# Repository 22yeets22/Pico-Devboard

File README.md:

<h1 align="center">
  Pico+ Devboard
  <br>
</h1>

<h4 align="center">
A pico sized custom rp2040 devboard, but with 16MB flash and a lot of extra features!
</h4>
<br>

<div align="center">

| Front Render                            | PCB                    |
| --------------------------------------- | ---------------------- |
|  |  |

</div>

## Motivation

I wanted a more capable RP2040 board with significantly more flash memory and USB-C. Most dev boards limit storage and input options, so I designed one that supports USB-C, battery input, higher current capability, and voltage monitoring while staying in the same form factor.

## Features

- RP2040 microcontroller
- 16MB QSPI Flash
- USB-C
- Battery input (Schottky diode OR-ing with USB)
- 500mA LDO (10V max input)
- VSYS voltage monitoring via resistor divider on ADC3
- Onboard power LED
- Onboard GPIO25 LED
- Bootsel + Reset button
- Fully labeled GPIO pins

## Future Improvements

- Buck-boost regulator for better efficiency + larger voltage range
- Exposed VSYS pin
- 3V3_EN pin breakout

## How to Use

Like a normal Pico:

1. Power the board via USB-C or VBAT input.
2. Flash firmware using BOOTSEL mode (or make your own)
3. Use onboard GPIO headers as you would with a standard Pico.

## Firmware

Untested waveshare 16mb - not my firmware, but has similar specs, so should work fine. Runs circuitpython.

## BOM

A complete `BOM.csv` with direct links is provided in BOM.csv in the root directory.
| Designator | Comment | Footprint | Manufacturer | Part Number | JLCPCB Part # | Link | Qty | Total Price ($) |
|------------|----------|------------|--------------|-------------|----------------|------|-----|-----------------|
| C1, C4 | 1uF | 0402 | Samsung | CL05A105KA5NQNC | C52923 | https://jlcpcb.com/partdetail/53938-CL05A105KA5NQNC/C52923 | 10 | 0.033 |
| C9 | 1nF | 0402 | FH | 0402B102K500NT | C1523 | https://jlcpcb.com/partdetail/1875-0402B102K500NT/C1523 | 5 | 0.006 |
| C11, C8, C3, C10, C17, C5, C7, C6, C12, C2 | 0.1uF | 0402 | Samsung | CL05B104KO5NNNC | C1525 | https://jlcpcb.com/partdetail/1877-CL05B104KO5NNNC/C1525 | 50 | 0.065 |
| C14, C13 | 10uF | 0603 | Samsung | CL10A106KP8NNNC | C19702 | https://jlcpcb.com/partdetail/20411-CL10A106KP8NNNC/C19702 | 10 | 0.065 |
| C16, C15 | 33pF | 0402 | FH | 0402CG330J500NT | C1562 | https://jlcpcb.com/partdetail/1914-0402CG330J500NT/C1562 | 10 | 0.012 |
| D2, D1 | LED (Red 0805) | 0805 | NationStar | NCD0805R1 | C84256 | https://jlcpcb.com/partdetail/85425-NCD0805R1/C84256 | 10 | 0.131 |
| D4, D3 | FMBR120VLSFT1G | SOD-123FL | FUXINSEMI | FMBR120VLSFT1G | C48677824 | https://jlcpcb.com/partdetail/FUXINSEMI-FMBR120VLSFT1G/C48677824 | 14 | 1.0444 |
| J1 | USB-C 14P | SMD | Hroparts | TYPE-C-31-M-12 | C165948 | https://jlcpcb.com/partdetail/Korean_HropartsElec-TYPE_C_31_M12/C165948 | 5 | 0.9055 |
| R1, R2 | 5.1K | 0402 | UNI-ROYAL | 0402WGF5101TCE | C25905 | https://jlcpcb.com/partdetail/26648-0402WGF5101TCE/C25905 | 10 | 0.008 |
| R4, R3 | 27Ω | 0402 | UNI-ROYAL | 0402WGF270JTCE | C25100 | https://jlcpcb.com/partdetail/25843-0402WGF270JTCE/C25100 | 22 | 0.0154 |
| R7 | 10K | 0402 | UNI-ROYAL | 0402WGF1002TCE | C25744 | https://jlcpcb.com/partdetail/26487-0402WGF1002TCE/C25744 | 5 | 0.004 |
| R9, R8, R5, R6 | 1K | 0402 | UNI-ROYAL | 0402WGF1001TCE | C11702 | https://jlcpcb.com/partdetail/12256-0402WGF1001TCE/C11702 | 20 | 0.014 |
| R10 | 200K | 0402 | UNI-ROYAL | 0402WGF2003TCE | C25764 | https://jlcpcb.com/partdetail/26507-0402WGF2003TCE/C25764 | 5 | 0.0035 |
| R11 | 100K | 0402 | UNI-ROYAL | 0402WGF1003TCE | C25741 | https://jlcpcb.com/partdetail/26484-0402WGF1003TCE/C25741 | 5 | 0.004 |
| SW2, SW1 | Tactile Switch | 4x3mm SMD | XUNPU | TS-1088-AR02016 | C720477 | https://jlcpcb.com/partdetail/XUNPU-TS_1088AR02016/C720477 | 10 | 0.476 |
| U1 | RP2040 | LQFN-56 | Raspberry Pi | RP2040 | C2040 | https://jlcpcb.com/partdetail/RaspberryPi-RP2040/C2040 | 5 | 4.827 |
| U2 | TPSPX3819M5-L-3-3 | SOT-23-5 | TECH PUBLIC | TPSPX3819M5-L-3-3 | C5370980 | https://jlcpcb.com/partdetail/TECHPUBLIC-TPSPX3819M5_L_33/C5370980 | 7 | 0.6839 |
| U3 | W25Q128JVSIQ | SOIC-8-208mil | Winbond | W25Q128JVSIQ | C97521 | https://jlcpcb.com/partdetail/WinbondElec-W25Q128JVSIQ/C97521 | 5 | 11.637 |
| Y1 | 12MHz Crystal | SMD3225-4P | YXC | X322512MSB4SI | C9002 | https://jlcpcb.com/partdetail/YXC_CrystalOscillators-X322512MSB4SI/C9002 | 5 | 0.363 |
| J3, J2 | 1x20 Pin Header | P2.54mm | — | Not Selected | — | — | — | — |
| J4 | 1x03 Pin Header | P2.54mm | — | Not Selected | — | — | — | — |

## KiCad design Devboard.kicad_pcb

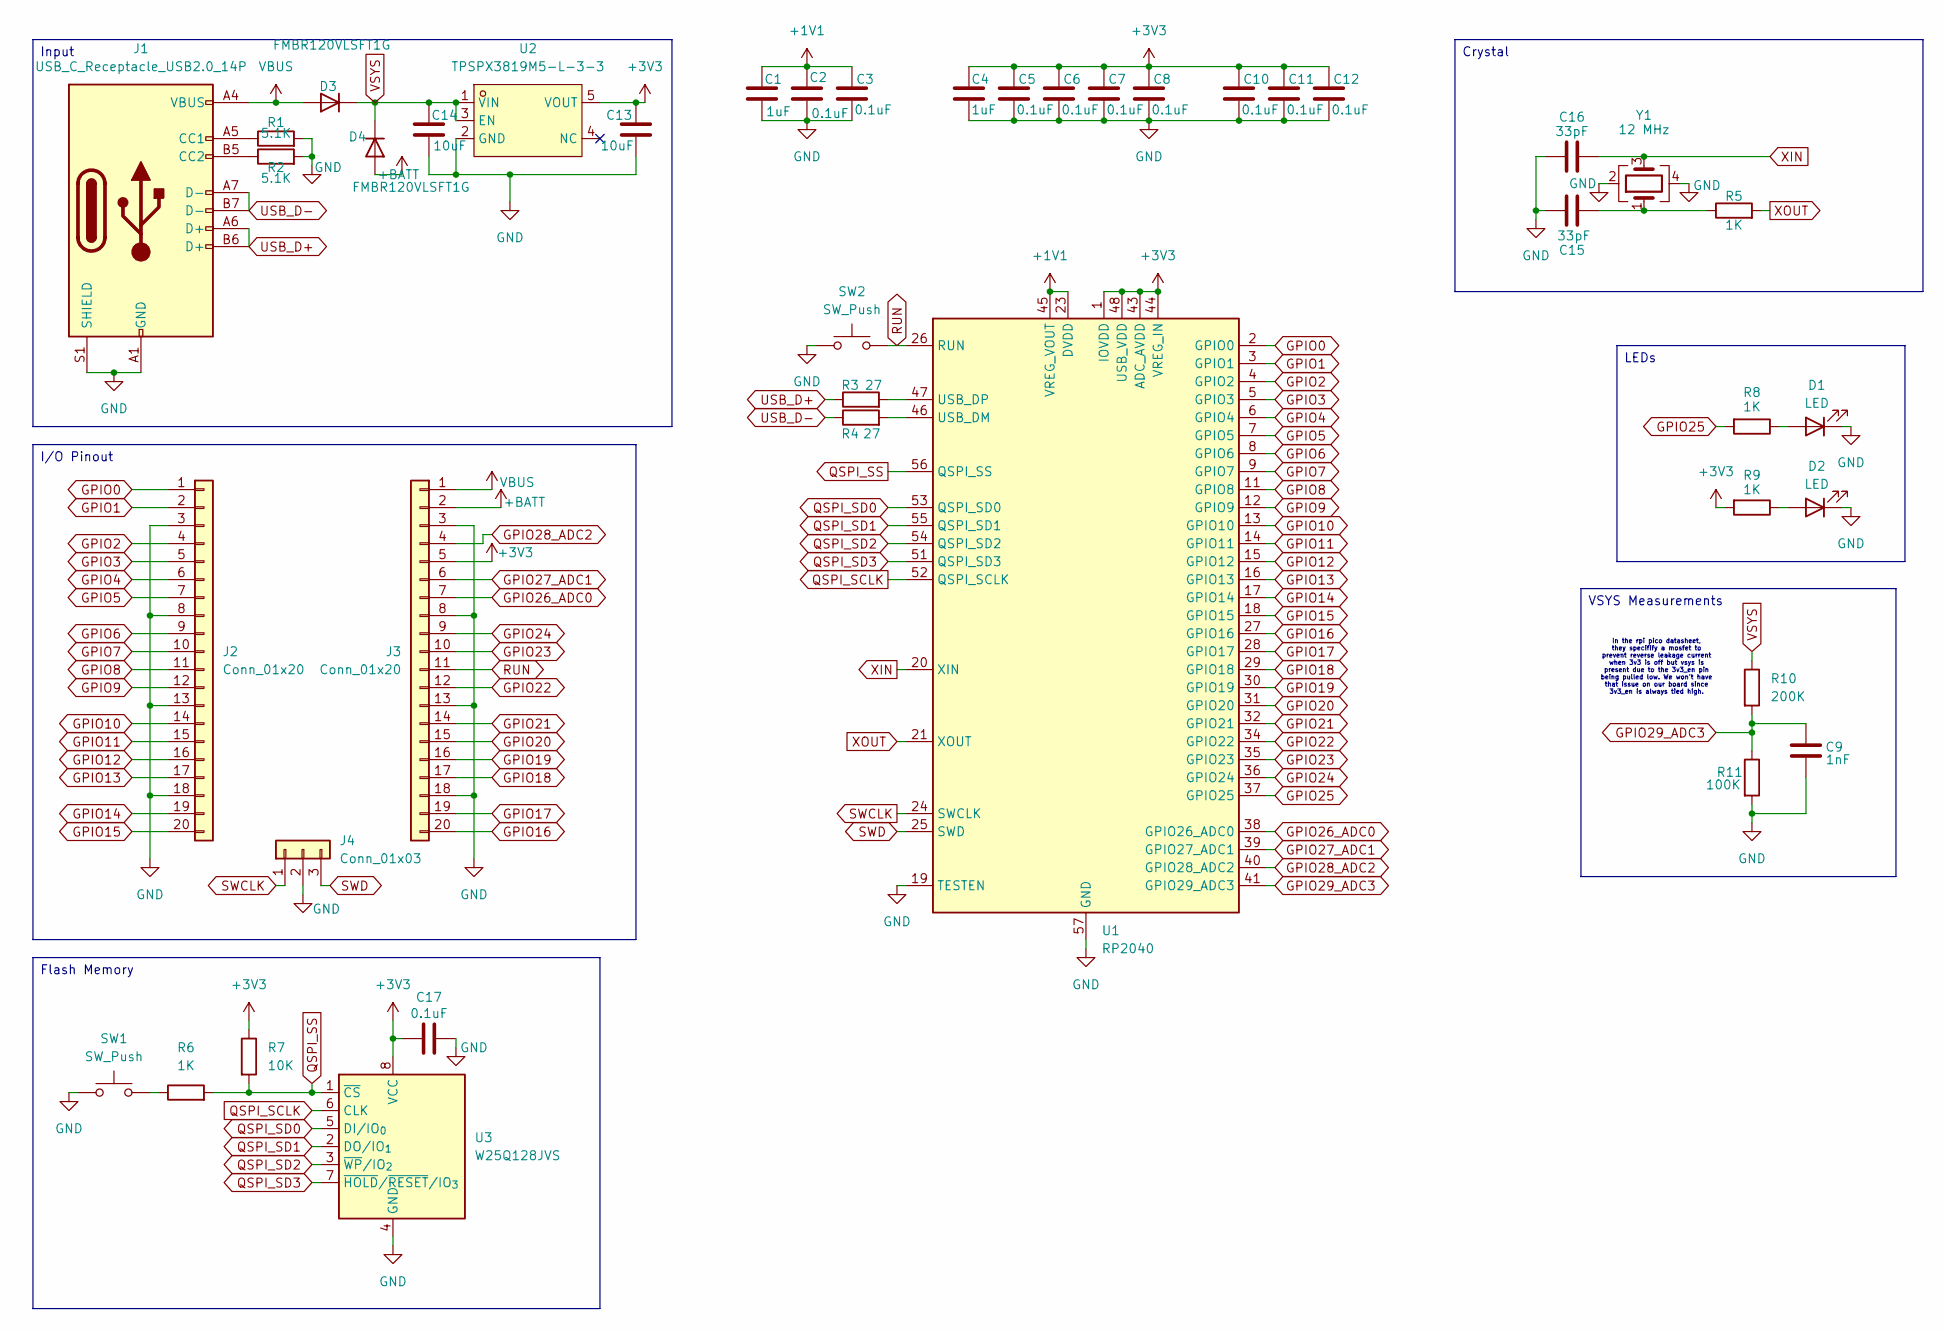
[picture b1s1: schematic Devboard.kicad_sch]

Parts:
C1, C4: 1uF; C_0402_1005Metric
C2, C3, C5, C6, C7, C8, C10, C11, C12, C17: 0.1uF; C_0402_1005Metric
C9: 1nF; C_0402_1005Metric
C13, C14: 10uF; C_0603_1608Metric
C15, C16: 33pF; C_0402_1005Metric
D1, D2: LED; LED_0805_2012Metric
D3, D4: FMBR120VLSFT1G; SOD-123FL_L2.8-W1.8-LS3.8-RD
J1: USB_C_Receptacle_USB2.0_14P; USB_C_Receptacle_HRO_TYPE-C-31-M-12
J2, J3: Conn_01x20; PinHeader_1x20_P2.54mm_Vertical
J4: Conn_01x03; PinHeader_1x03_P2.54mm_Vertical
R1, R2: 5.1K; R_0402_1005Metric
R3, R4: 27; R_0402_1005Metric
R5, R6, R8, R9: 1K; R_0402_1005Metric
R7: 10K; R_0402_1005Metric
R10: 200K; R_0402_1005Metric
R11: 100K; R_0402_1005Metric
SW1, SW2: SW_Push; SW_Push_SPST_NO_Alps_SKRK
U1: RP2040; QFN-56-1EP_7x7mm_P0.4mm_EP3.2x3.2mm
U2: TPSPX3819M5-L-3-3; SOT-23-5_L3.0-W1.6-P0.95-LS2.8-BR; LCSC Part C5370980
U3: W25Q128JVS; SOIC-8_5.3x5.3mm_P1.27mm
Y1: 12 MHz; Crystal_SMD_3225-4Pin_3.2x2.5mm

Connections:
+1V1: C1.1, C2.1, C3.1, U1.23 (DVDD), U1.45 (VREG_VOUT), U1.50 (DVDD)
+3V3: C4.1, C5.1, C6.1, C7.1, C8.1, C10.1, C11.1, C12.1, C13.1, C17.1, J3.5, R7.1, R9.2, U1.1 (IOVDD), U1.10 (IOVDD), U1.22 (IOVDD), U1.33 (IOVDD), U1.42 (IOVDD), U1.43 (ADC_AVDD), U1.44 (VREG_IN), U1.48 (USB_VDD), U1.49 (IOVDD), U2.5 (VOUT), U3.8 (VCC)
+BATT: D4.2 (A), J3.2
GND: C1.2, C2.2, C3.2, C4.2, C5.2, C6.2, C7.2, C8.2, C9.2, C10.2, C11.2, C12.2, C13.2, C14.2, C15.1, C16.1, C17.2, D1.1 (K), D2.1 (K), J1.A1 (GND), J1.A12 (GND), J1.B1 (GND), J1.B12 (GND), J1.S1 (SHIELD), J2.3, J2.8, J2.13, J2.18, J3.3, J3.8, J3.13, J3.18, J4.2, R1.2, R2.2, R11.2, SW1.1, SW2.2, U1.19 (TESTEN), U1.57 (GND), U2.2 (GND), U3.4 (GND), Y1.2, Y1.4
GPIO0: J2.1, U1.2 (GPIO0)
GPIO1: J2.2, U1.3 (GPIO1)
GPIO2: J2.4, U1.4 (GPIO2)
GPIO3: J2.5, U1.5 (GPIO3)
GPIO4: J2.6, U1.6 (GPIO4)
GPIO5: J2.7, U1.7 (GPIO5)
GPIO6: J2.9, U1.8 (GPIO6)
GPIO7: J2.10, U1.9 (GPIO7)
GPIO8: J2.11, U1.11 (GPIO8)
GPIO9: J2.12, U1.12 (GPIO9)
GPIO10: J2.14, U1.13 (GPIO10)
GPIO11: J2.15, U1.14 (GPIO11)
GPIO12: J2.16, U1.15 (GPIO12)
GPIO13: J2.17, U1.16 (GPIO13)
GPIO14: J2.19, U1.17 (GPIO14)
GPIO15: J2.20, U1.18 (GPIO15)
GPIO16: J3.20, U1.27 (GPIO16)
GPIO17: J3.19, U1.28 (GPIO17)
GPIO18: J3.17, U1.29 (GPIO18)
GPIO19: J3.16, U1.30 (GPIO19)
GPIO20: J3.15, U1.31 (GPIO20)
GPIO21: J3.14, U1.32 (GPIO21)
GPIO22: J3.12, U1.34 (GPIO22)
GPIO23: J3.10, U1.35 (GPIO23)
GPIO24: J3.9, U1.36 (GPIO24)
GPIO25: R8.2, U1.37 (GPIO25)
GPIO26_ADC0: J3.7, U1.38 (GPIO26_ADC0)
GPIO27_ADC1: J3.6, U1.39 (GPIO27_ADC1)
GPIO28_ADC2: J3.4, U1.40 (GPIO28_ADC2)
GPIO29_ADC3: C9.1, R10.2, R11.1, U1.41 (GPIO29_ADC3)
unnamed: C15.2, R5.1, Y1.1
unnamed: D1.2 (A), R8.1
unnamed: D2.2 (A), R9.1
unnamed: J1.A5 (CC1), R1.1
unnamed: J1.B5 (CC2), R2.1
unnamed: R6.1, SW1.2
unnamed: R4.2, U1.46 (USB_DM)
unnamed: R3.2, U1.47 (USB_DP)
QSPI_SCLK: U1.52 (QSPI_SCLK), U3.6 (CLK)
QSPI_SD0: U1.53 (QSPI_SD0), U3.5 (DI/IO_{0})
QSPI_SD1: U1.55 (QSPI_SD1), U3.2 (DO/IO_{1})
QSPI_SD2: U1.54 (QSPI_SD2), U3.3 (~WP/IO_{2})
QSPI_SD3: U1.51 (QSPI_SD3), U3.7 (~HOLD/~RESET/IO_{3})
QSPI_SS: R6.2, R7.2, U1.56 (QSPI_SS), U3.1 (~CS)
RUN: J3.11, SW2.1, U1.26 (RUN)
SWCLK: J4.1, U1.24 (SWCLK)
SWD: J4.3, U1.25 (SWD)
USB_D+: J1.A6 (D+), J1.B6 (D+), R3.1
USB_D-: J1.A7 (D-), J1.B7 (D-), R4.1
VBUS: D3.2 (A), J1.A4 (VBUS), J1.A9 (VBUS), J1.B4 (VBUS), J1.B9 (VBUS), J3.1
VSYS: C14.1, D3.1 (K), D4.1 (K), R10.1, U2.1 (VIN), U2.3 (EN)
XIN: C16.2, U1.20 (XIN), Y1.3
XOUT: R5.2, U1.21 (XOUT)

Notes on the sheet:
In the rpi pico datasheet, they specifify a mosfet to prevent reverse leakage current when 3v3 is off but vsys is present due to the 3v3_en pin being pulled low. We won't have that issue on our board since 3v3_en is always tied high.
Input
LEDs
VSYS Measurements
Flash Memory
I/O Pinout
Crystal

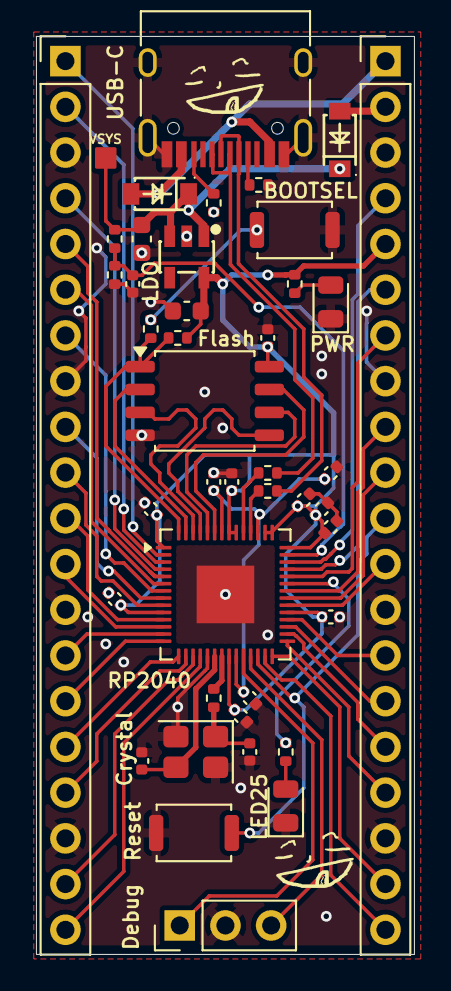
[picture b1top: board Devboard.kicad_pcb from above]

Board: 2 copper layers, 21.0 x 51.0 mm, 42 parts (0 on the bottom side), 57 nets.

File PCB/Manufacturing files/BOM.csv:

Id,Designator,Footprint,Quantity,Comment,Supplier and ref
1,"SW2,SW1",SW_Push_SPST_NO_Alps_SKRK,2,SW_Push,
2,"C16,C15",C_0402_1005Metric,2,33pF,
3,U2,SOT-23-5_L3.0-W1.6-P0.95-LS2.8-BR,1,TPSPX3819M5-L-3-3,
4,R11,R_0402_1005Metric,1,100K,
5,R10,R_0402_1005Metric,1,200K,
6,"D4,D3",SOD-123FL_L2.8-W1.8-LS3.8-RD,2,FMBR120VLSFT1G,
7,C9,C_0402_1005Metric,1,1nF,
8,J1,USB_C_Receptacle_HRO_TYPE-C-31-M-12,1,USB_C_Receptacle_USB2.0_14P,
9,"C11,C8,C3,C10,C17,C5,C7,C6,C12,C2",C_0402_1005Metric,10,0.1uF,
10,"R4,R3",R_0402_1005Metric,2,27,
11,"C1,C4",C_0402_1005Metric,2,1uF,
12,"R1,R2",R_0402_1005Metric,2,5.1K,
13,J4,PinHeader_1x03_P2.54mm_Vertical,1,Conn_01x03,
14,"C14,C13",C_0603_1608Metric,2,10uF,
15,"D2,D1",LED_0805_2012Metric,2,LED,
16,R7,R_0402_1005Metric,1,10K,
17,"R9,R8,R5,R6",R_0402_1005Metric,4,1K,
18,"J3,J2",PinHeader_1x20_P2.54mm_Vertical,2,Conn_01x20,
19,Y1,Crystal_SMD_3225-4Pin_3.2x2.5mm,1,12 MHz,
20,U1,QFN-56-1EP_7x7mm_P0.4mm_EP3.2x3.2mm,1,RP2040,
21,U3,SOIC-8_5.3x5.3mm_P1.27mm,1,W25Q128JVS,

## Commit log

2026-02-16 rename - add files
2026-02-16 Images
2026-02-16 Better readme
2026-02-16 readme fix + 3d model
2026-02-16 reorganize, readme
2026-02-16 new bom
2026-02-16 simple firmware + test code
2026-02-16 add schematic but not in readme
2026-02-16 looks readme
2026-03-10 Fix header formatting in README.md
2026-05-21 add final product
